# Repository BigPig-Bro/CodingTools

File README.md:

# Coding Tools

## 描述：

​	本仓库下收录了本人常用一些FPGA工作常用的工具和手册。

## 分类

**软件工具类：**

+ **mif_coe_Convert**: 用于Altera 的 FPGA和Xilinx的FPGA的ROM初始化文件相互转换，目前完成了MIF2COE，将exe文件放置mif文件同目录下，点击运行，自动生成对应的coe文件。
+ **串口调试助手**:目前用的纸飞机，付费软件，功能挺多。
+ **图片文字取模**：包含BMP2LCD、BMP2YCBCR以及取模工具等。
+ **代码模板**：自用的一些Verilog轮子，不熟悉者慎用。

**文档手册类**

+ **Xilinx 系列**：Xilinx下面FPGA的手册，包含常见的A7、K7、ZYNQ等。
+ **Altera 系列**：Altera下面FPGA的手册，包含常见的大风4、5、10等。
+ **Gowin系列**：国产FPGA 高云系列手册
+ **Anlogic系列**：国产FPGA 安路系列手册
+ **Pango系列**：国产FPGA 紫光系列手册
+ **AGM系列**：国产FPGA 傲格芯系列手册
+ **OV摄像头手册**：包含5640、5642、7670等常见型号。
+ **WCH系列手册**：包含CH340等。
+ **RAM系列手册**：包含海力士和镁光的SDRAM，未来考虑加入DDR。
+ **ROM系列手册**：包含W25P16等系列FLASH等
+ **ADC_DAC系列手册**：常见的一些比较好使的ADDA芯片，如AD9708\9228等
+ **USB系列**：包含一些JTAG、USB传输芯片等
+ **Video_Timing**：包含标准的一些视频时序参数
+ **传感器类**：包含各种温湿度等环境传感器
+ **单片机系列**：包含低端的各种51 32系列，不常用
+ **电源芯片系列**：包含LDO\DCDC\负压芯片等
+ **接口转换系列**：包含HDMI编解码等芯片
+ **以太网卡系列**：包含IP\RTL等系列网卡芯片
+ ……

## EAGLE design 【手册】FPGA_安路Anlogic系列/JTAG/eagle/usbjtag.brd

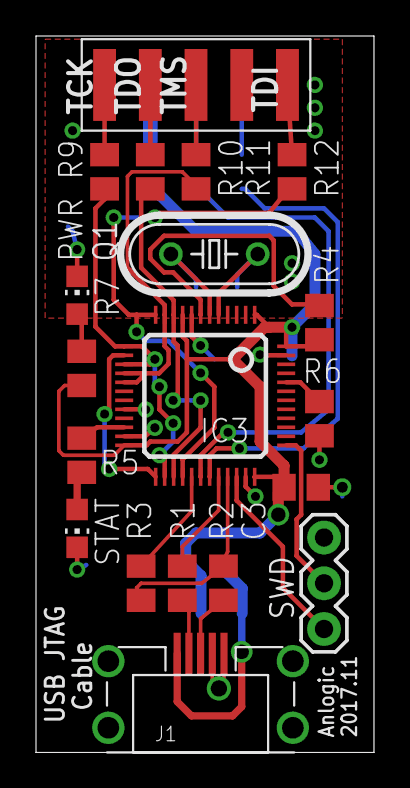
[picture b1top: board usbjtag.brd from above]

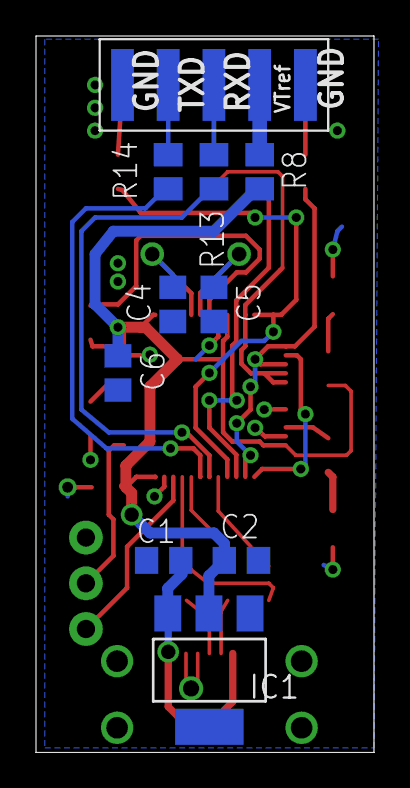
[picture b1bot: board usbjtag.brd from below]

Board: 2 copper layers, 18.8 x 39.8 mm, 29 parts (10 on the bottom side), 31 nets.

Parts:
C1, C2: 10u; C0805
C3, C6: 104; C0805
C4, C5: 22p; C0805
CON1, CON2: SIDESMT
IC1: REG1117; SOT223
IC3: STM32F10XCXT6; TQFP48
J1: USB-MICROB4Z; MICROUSB_4Z
PWR: CHIP-LED0805
Q1: 8M; HC49/S
R1, R2, R9, R10, R11, R12, R13, R14: 22; M0805
R3, R4, R5, R6, R7: 1.5k; M0805
R8: DNP; M0805
STAT: CHIP-LED0805
SWD: 1X03

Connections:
+3V3: C2.1, C3.1, C6.1, IC1.2, IC3.1, IC3.9, IC3.24, IC3.36, IC3.48, R4.2, R7.2, R8.2
+5V: C1.1, IC1.3, J1.VBUS
GND: C1.2, C2.2, C3.2, C4.2, C5.2, C6.2, CON2.1, CON2.5, IC1.1, IC3.8, IC3.20, IC3.23, IC3.35, IC3.47, J1.GND, J1.ID, J1.SHEILD1, J1.SHEILD2, J1.SHEILD3, J1.SHEILD4, PWR.C, R6.2, STAT.C, SWD.1
JTAG_TCK: IC3.13, IC3.15, IC3.26, R9.2
JTAG_TDI: IC3.12, IC3.28, R12.2
JTAG_TDO: IC3.10, IC3.27, R10.2
JTAG_TMS: IC3.11, IC3.16, IC3.17, R11.2
unnamed: J1.D-, R1.1
unnamed: J1.D+, R2.1
unnamed: IC3.34, SWD.3
unnamed: PWR.A, R7.1
unnamed: IC3.37, SWD.2
unnamed: CON1.5, R9.1
unnamed: CON2.3, R13.1
unnamed: CON1.4, R10.1
unnamed: CON2.2, R14.1
unnamed: CON1.3, R11.1
unnamed: CON1.1, R12.1
unnamed: IC3.32, R1.2
unnamed: IC3.33, R2.2, R3.2
unnamed: IC3.29, R3.1
unnamed: IC3.7, R4.1
unnamed: IC3.22, R5.1
unnamed: R5.2, STAT.A
unnamed: C4.1, IC3.5, Q1.2
unnamed: C5.1, IC3.6, Q1.1
unnamed: IC3.44, R6.1
SPI_CS: IC3.14, IC3.25
UART_RXD: IC3.31, R14.2
UART_TXD: IC3.30, R13.2
VCCINT: CON2.4, R8.1

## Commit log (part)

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2023-05-06 一键 MIF COE文件互转脚本
2023-05-10 资料更新
2023-05-22 图片工具
2023-05-22 ZYNQ资料
2023-05-22 更新文档
2023-05-29 更新分类
2023-05-31 日常更新
2023-06-10 更新备份
2023-06-11 更新文件
2023-06-12 更新手册
2023-12-08 1208 同步手册文档
2024-01-24 20240124 日常更新
2024-04-17 20240417 更新最终版 实现mif coe双向转换
2024-04-20 20240420 更新文档
2025-06-15 250615 更新代码和语法规范
2025-07-05 250705 更新

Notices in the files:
parts and their libraries:
SparkFun-Connectors: Licensing: Creative Commons ShareAlike 4.0 International - https://creativecommons.org/licenses/by-sa/4.0
